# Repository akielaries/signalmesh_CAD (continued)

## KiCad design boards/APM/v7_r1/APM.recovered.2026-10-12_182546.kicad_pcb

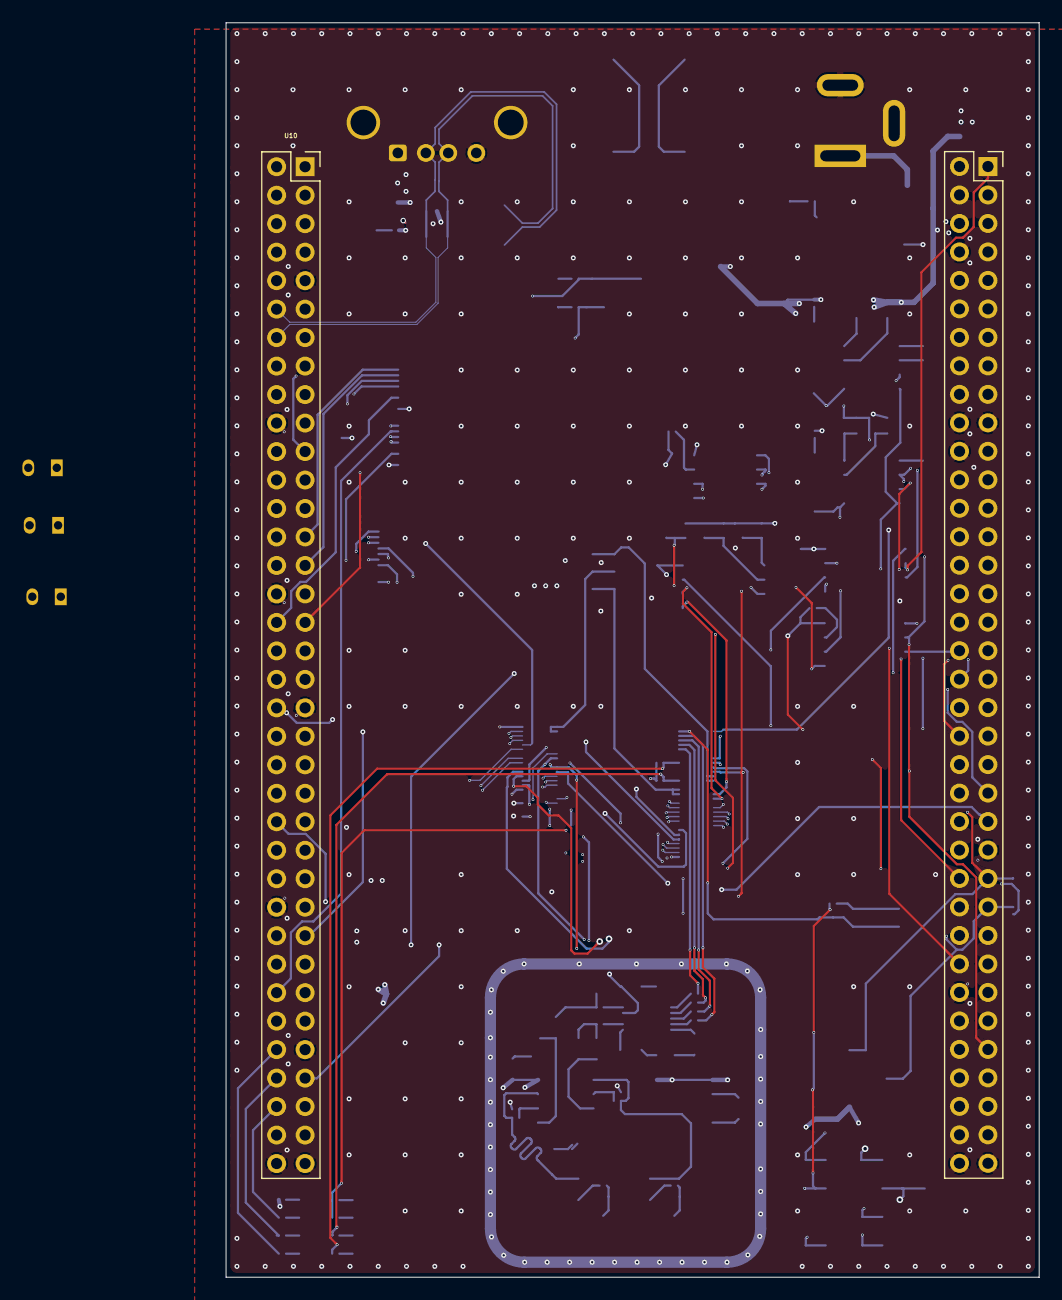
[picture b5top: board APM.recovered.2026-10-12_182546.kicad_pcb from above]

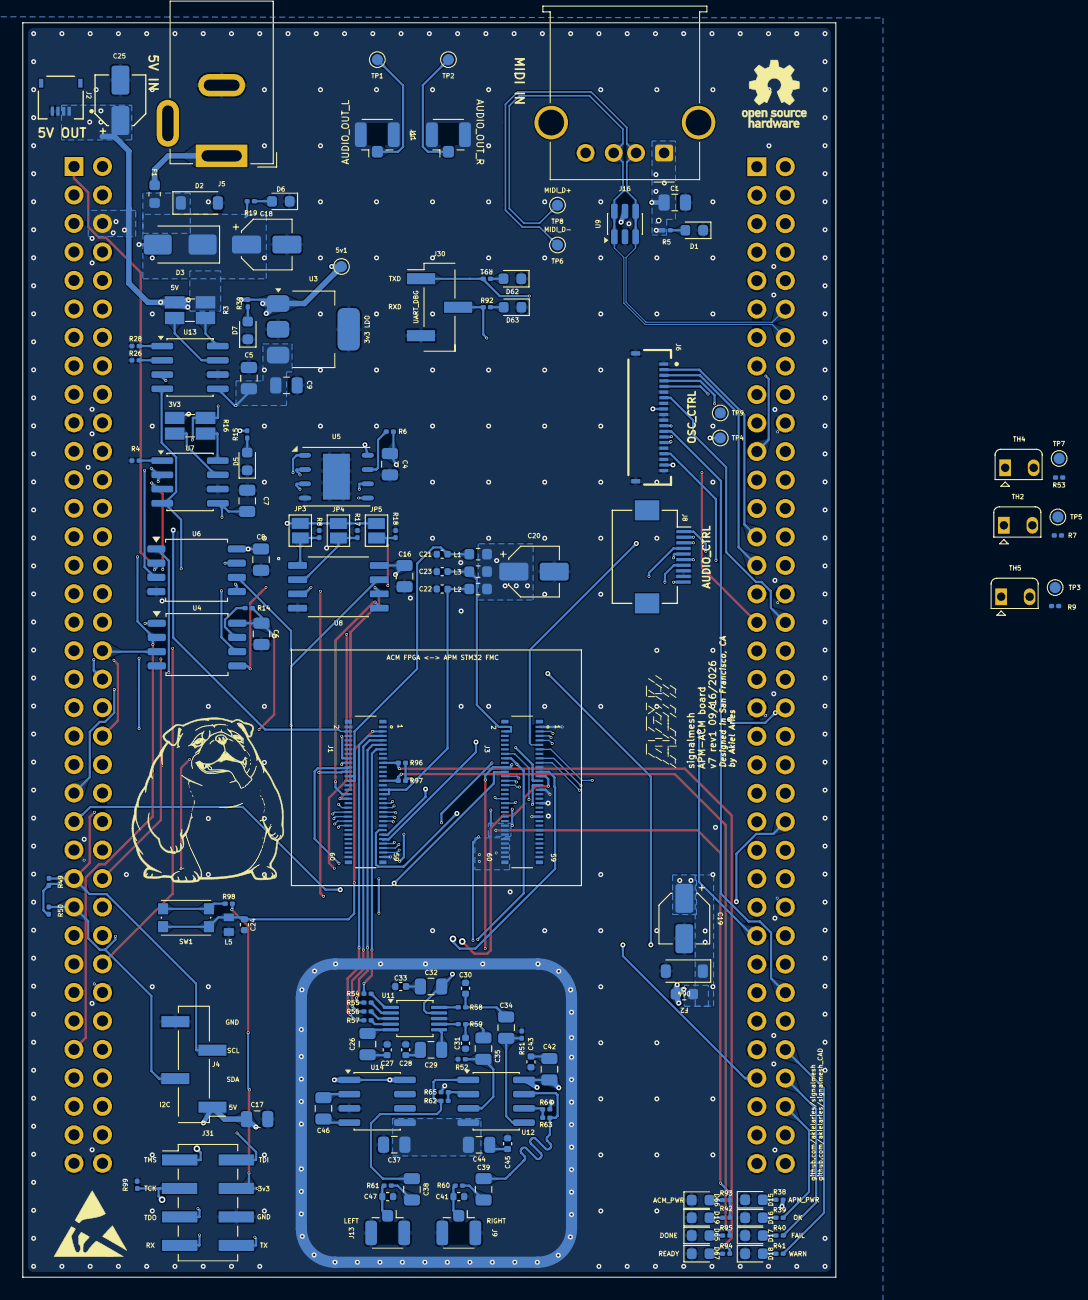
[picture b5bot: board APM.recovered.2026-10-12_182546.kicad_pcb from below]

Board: 6 copper layers, 72.5 x 111.9 mm, 151 parts (149 on the bottom side), 161 nets.

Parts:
5v1: 5v; TestPoint_Pad_D1.0mm
C1: 22pf; C_0805_2012Metric
C4, C6, C8, C9, C16, C17: 100nF; C_0805_2012Metric
C5, C7: 0.1uf; C_0805_2012Metric
C18, C19, C20, C25: 220uF 10V; CP_Elec_4x3
C21, C22, C23, C24: 100nF; C_0402_1005Metric
C26, C29, C32, C34, C35, C38, C39, C42, C44, C46: 10uF; C_0805_2012Metric
C27, C28, C33, C43, C45: 0.1uF; C_0402_1005Metric
C30, C31: 2.7nF; C_0402_1005Metric
C37: 100uF; C_0805_2012Metric
C41, C47: 47pF; C_0402_1005Metric
D1, D5, D7: LED_PWR; LED_0603_1608Metric
D2, D64: 20V 3A; D_SOD-123
D3: SMAJ5.0A; D_SMA
D6: RED_LED_PWR; LED_0603_1608Metric
D15: PWR; LED_0603_1608Metric
D16: OK; LED_0603_1608Metric
D17: FAIL; LED_0603_1608Metric
D18: WARN; LED_0603_1608Metric
D19: FPGA_PWR; LED_0603_1608Metric
D62: TXD; LED_0603_1608Metric
D63: RXD; LED_0603_1608Metric
D65, D66, D67: GREEN_LED; LED_0603_1608Metric
F1, F2: 6V 2A; Fuse_0603_1608Metric
J1, J3: DF40C-60DS-0.4V(51); Hirose_DF40C-60DS-0.4V_2x30_P0.4mm
J2: AUDIO_PWR; AMPHENOL_F3311A7H121004E200
J4: LCD_display; PinHeader_1x04_P2.54mm_Vertical_SMD_Pin1Left
J5: Barrel_Jack; BarrelJack_GCT_DCJ200-10-A_Horizontal
J6: OSC_CTRL; GCT_FFC2B28-20-G
J7: DAC_R_PRB; U.FL_Hirose_U.FL-R-SMT-1_Vertical
J8: AUDIO_CTRL; Hirose_FH12-10S-0.5SH_1x10-1MP_P0.50mm_Horizontal
J9: ACM_DAC_R; U.FL_Hirose_U.FL-R-SMT-1_Vertical
J11: DAC_L_PRB; U.FL_Hirose_U.FL-R-SMT-1_Vertical
J13: ACM_DAC_L; U.FL_Hirose_U.FL-R-SMT-1_Vertical
J16: USB_A_FEMALE; USB_A_Molex_67643_Horizontal
J30: UART_DEBUG; PinHeader_1x03_P2.54mm_Vertical_SMD_Pin1Left
J31: Conn_02x04_Odd_Even; PinHeader_2x04_P2.54mm_Vertical_SMD
JP3: A0; SolderJumper-2_P1.3mm_Open_Pad1.0x1.5mm
JP4: A1; SolderJumper-2_P1.3mm_Open_Pad1.0x1.5mm
JP5: A2; SolderJumper-2_P1.3mm_Open_Pad1.0x1.5mm
L1, L2, L3: PZ1608D300-3R0TF; L_0603_1608Metric
L5: LXES15AAA1-153; INDC1005X45
R3, R16: 0.1; R_Shunt_Ohmite_LVK12
R4, R6, R7, R8, R9, R14, R17, R18, R26, R28, R53: 10k; R_0201_0603Metric
R5, R15, R30, R39, R40, R41, R42, R91, R92: 300; R_0201_0603Metric
R19, R93, R94, R95: 4.7k; R_0201_0603Metric
R38: 1.2k; R_0201_0603Metric
R49, R50: 2.2k; R_0201_0603Metric
R51, R52: 47k; R_0201_0603Metric
R54, R55, R56, R57: 22; R_0201_0603Metric
R58, R59: 560; R_0201_0603Metric
R60, R61: 100; R_0201_0603Metric
R62, R63: 1k; R_0201_0603Metric
R64, R65: 2k; R_0201_0603Metric
R96, R97: 49.9k; R_0201_0603Metric
R98: 100R; R_0201_0603Metric
R99: 5.1K; R_0201_0603Metric
SW1: RST; SW_Push_1P1T_NO_CK_KMR2
TH2, TH4, TH5: 10k; Heraeus_TO-92-2
TP1: DAC_L; TestPoint_Pad_D1.0mm
TP2: DAC_R; TestPoint_Pad_D1.0mm
TP3: THRM_A; TestPoint_Pad_D1.0mm
TP4: FPC_3V3_TP; TestPoint_Pad_D1.0mm
TP5: THRM_C; TestPoint_Pad_D1.0mm
TP6: MIDI_D-; TestPoint_Pad_D1.0mm
TP7: THRM_E; TestPoint_Pad_D1.0mm
TP8: MIDI_D+; TestPoint_Pad_D1.0mm
TP9: FPC_GND_TP; TestPoint_Pad_D1.0mm
U1, U10: PinSocket_2x36_P2.54mm_Vertical
U3: LT1963AxST-3.3; SOT-223-3_TabPin2
U4, U6: W25Q128JVS; SOIC-8_5.3x5.3mm_P1.27mm
U5: MR25H40; DFN-S-8-1EP_6x5mm_P1.27mm
U7, U13: INA219AxD; SOIC-8_3.9x4.9mm_P1.27mm
U8: 24LC1025-I_P; SOIC127P794X202-8N
U9: USBLC6-2SC6; SOT-23-6
U11: CS4344; TSSOP-10_3x3mm_P0.5mm
U12: OPA1656ID; SOIC-8_3.9x4.9mm_P1.27mm
U14: LTC660; SOIC-8_3.9x4.9mm_P1.27mm

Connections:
3V3_APM: C4.1, C6.1, C8.1, C16.1, C32.2, J6.9, J6.19, JP3.2 (B), JP4.2 (B), JP5.2 (B), R6.1, R14.1, R15.2, R16.4, R49.2, R50.2, TP4.1 (1_1), U4.8 (VCC), U5.8 (VDD), U6.8 (VCC), U8.8 (VCC), U11.9 (VA)
3V3_LDO: C5.2, C7.2, C9.1, R16.1, U3.3 (OUT), U7.2 (A0), U7.5 (VS), U13.5 (VS)
5V_APM: 5v1.1 (1_1), C1.2, C17.2, C25.1, C42.2, F2.2, J2.1, J2.2, J4.1, J16.1 (VBUS), R3.4, R5.2, R30.2, R38.2, U1.6 (5V_EXT), U3.1 (IN), U9.5 (VBUS), U12.8 (V+), U14.1 (BOOST), U14.8 (V+)
-5V: C37.1, C44.2, U12.4 (V-), U14.5 (VOUT)
/ADC_POT_1: J6.7, U10.34 (PC4)
/ADC_POT_2: J6.17, U10.36 (PF5)
/APM_DBG_RX: J30.2, R92.1, U10.33 (PA10)
/APM_DBG_TX: J30.1, R91.1, U10.21 (PA9)
/APM_EEPROM_EN: U1.44 (PG3), U8.7 (WP)
/APM_FMC_A16: J3.28, U10.45 (PD11)
/APM_FMC_A17: J3.26, U10.43 (PD12)
/APM_FMC_A18: J3.24, U10.41 (PD13)
/APM_FMC_A19: J3.22, U1.47 (PE3)
/APM_FMC_A20: J1.38, U1.48 (PE4)
/APM_FMC_A21: J1.40, U1.50 (PE5)
/APM_FMC_A22: J1.44, U1.62 (PE6)
/APM_FMC_A23: J1.42, U1.46 (PE2)
/APM_FMC_A24: J1.46, U1.68 (PG13)
/APM_FMC_CLK: J3.34, U1.40 (PD3)
/APM_FMC_DA0: J3.36, U10.46 (PD14)
/APM_FMC_DA1: J1.47, U10.48 (PD15)
/APM_FMC_DA2: J1.41, U1.57 (PD0)
/APM_FMC_DA3: J1.39, U1.55 (PD1)
/APM_FMC_DA4: J3.7, U10.44 (PE7)
/APM_FMC_DA5: J3.5, U10.40 (PE8)
/APM_FMC_DA6: J1.49, U10.52 (PE9)
/APM_FMC_DA7: J3.11, U10.47 (PE10)
/APM_FMC_DA8: J1.51, U10.56 (PE11)
/APM_FMC_DA9: J3.14, U10.49 (PE12)
/APM_FMC_DA10: J3.3, U10.55 (PE13)
/APM_FMC_DA11: J3.15, U10.51 (PE14)
/APM_FMC_DA12: J3.17, U10.53 (PE15)
/APM_FMC_DA13: J1.55, U10.10 (PD8)
/APM_FMC_DA14: J1.43, U1.69 (PD9)
/APM_FMC_DA15: J1.53, U10.65 (PD10)
/APM_FMC_NE1: J3.9, U10.19 (PC7)
/APM_FMC_NL: J1.4, U1.21 (PB7)
/APM_FMC_NOE: J1.35, U1.39 (PD4)
/APM_FMC_NWAIT: J1.57, U10.4 (PC6)
/APM_FMC_NWE: J1.37, U1.41 (PD5)
/APM_FPGA_UART_RX: J3.16, J31.7, U10.23 (PA8)
/APM_FPGA_UART_TX: J3.20, J31.8, U10.31 (PB3)
/APM_I2C2_SCL: J1.34, J4.3, R49.1, U1.51 (PF1), U7.4 (SCL), U8.6 (SCL), U13.4 (SCL)
/APM_I2C2_SDA: J1.32, J4.2, R50.1, U1.53 (PF0), U7.3 (SDA), U8.5 (SDA), U13.3 (SDA)
/APM_LED_FAIL: R40.2, U10.66 (PG8)
/APM_LED_OK: R39.2, U10.68 (PG5)
/APM_LED_WARN: R41.2, U10.64 (PE0)
/APM_MRAM_EN: U1.38 (PC0), U5.3 (~WP)
/APM_SPI1_CS: J1.20, U1.66 (PG10)
/APM_SPI1_MISO: J1.18, U1.63 (PG9), U4.2 (DO/IO_{1}), U5.2 (SO)
/APM_SPI1_MOSI: J1.16, U1.45 (PD7), U4.5 (DI/IO_{0}), U5.5 (SI)
/APM_SPI1_SCK: J1.22, U1.70 (PG11), U4.6 (CLK), U5.6 (SCK)
/APM_SPI2_MISO: J8.3, U10.28 (PB14)
/APM_SPI2_MOSI: J8.2, U10.26 (PB15)
/APM_SPI2_SCK: J8.1, U10.30 (PB13)
/APM_SPIFLASH_EN: U1.36 (PC1), U4.3 (~WP/IO_{2})
/AUD_CS_DAC: J8.4, U1.43 (PD6)
/AUD_CS_POTS: J8.5, U1.52 (PF2)
/AUD_GATE: J8.7, U1.59 (PG0)
/AUD_MODE: J8.6, U1.42 (PG2)
/AUD_SPARE: J8.10, U1.58 (PG1)
/DAC_1-1_R: J7.1 (In), TP2.1 (1_1)
/DAC_1-2_L: J11.1 (In), TP1.1 (1_1)
/FPGA_INTERFACE/A2_JTAG_TDO: J3.25, J31.5
/FPGA_INTERFACE/A3_JTAG_TDI: J3.27, J31.2
/FPGA_INTERFACE/B1_JTAG_TMS: J3.23, J31.1
/FPGA_INTERFACE/C1_JTAG_TCK: J3.21, J31.3, R99.1
/FPGA_INTERFACE/D7_DONE: J1.25, R95.2, R97.1
/FPGA_INTERFACE/E8_READY: J1.17, R94.2, R96.1
/FPGA_INTERFACE/FPGA_3V3: C20.1, J3.46, J3.48, J3.50, J31.4, L1.2, L2.2, L3.2, R42.2, R93.2, R96.2, R97.2, R98.2
/FPGA_INTERFACE/H11_IOT3A_S1: C24.2, J1.3, L5.2, SW1.2
/FPGA_INTERFACE/LED_DONE_A: D65.2 (A), R95.1
/FPGA_INTERFACE/LED_PWR_A: D66.2 (A), R93.1
/FPGA_INTERFACE/LED_READY_A: D67.2 (A), R94.1
/FPGA_INTERFACE/RST_NODE: R98.1, SW1.1
/FPGA_INTERFACE/VCCIO01: C21.1, J1.24, J1.26, L1.1
/FPGA_INTERFACE/VCCIO23: C23.2, J3.2, J3.4, L3.1
/FPGA_INTERFACE/VCCIO67: C22.2, J1.29, J1.31, L2.1
/MIDI_FS_D+: J16.3 (D+), TP8.1 (1_1), U9.1 (I/O1), U9.6 (I/O1), U10.14 (PA11)
/MIDI_FS_D-: J16.2 (D-), TP6.1 (1_1), U9.3 (I/O2), U9.4 (I/O2), U10.12 (PA12)
/NC: U1.25 (PC14), U1.27 (PC15), U1.29 (PH0)
/PMS_APM/5V_PWR_IN: C18.1, D2.1 (K), D3.1 (K), F1.1, R3.1, R19.2
/QSPI1_D0: U6.5 (DI/IO_{0}), U10.1 (PC9)
/QSPI1_D1: U1.1 (PC10), U6.2 (DO/IO_{1})
/QSPI1_D2: U1.11 (PF7), U6.3 (~WP/IO_{2})
/QSPI1_D3: U1.30 (PA1), U6.7 (~HOLD/~RESET/IO_{3})
/QSPI1_NCS: U6.1 (~CS), U10.70 (PG6)
/QSPI_SCK2: U6.6 (CLK), U10.42 (PF10)
/SEL_A_BIT_0: J6.2, U10.27 (PB4)
/SEL_A_BIT_1: J6.3, U10.29 (PB5)
/SEL_A_BIT_2: J6.4, U10.24 (PB1)
/SEL_A_BIT_3: J6.5, U10.17 (PB6)
/SEL_B_BIT_0: J6.12, U10.16 (PB12)
/SEL_B_BIT_1: J6.13, U10.60 (PF15)
/SEL_B_BIT_2: J6.14, U10.13 (PA6)
/SEL_B_BIT_3: J6.15, U10.15 (PA7)
/SPIFLASH_CS: U1.34 (PB0), U4.1 (~CS)
/SPIMRAM_CS: U1.28 (PA0), U5.1 (~CS)
/THRM_A: R9.2, TP3.1 (1_1)
/THRM_C: R7.2, TP5.1 (1_1)
/THRM_E: R53.2, TP7.1 (1_1)
ACM_DAC_LRCK: J1.7, R56.1
ACM_DAC_MCLK: J1.5, R57.1
ACM_DAC_SCLK: J1.9, R55.1
ACM_DAC_SDIN: J1.11, R54.1
FPGA_5V: C19.1, D64.1 (K), F2.1, J3.52, J3.54, J3.56, J3.58, J3.60
GND: C1.1, C4.2, C5.1, C6.2, C7.1, C8.2, C9.2, C16.2, C17.1, C18.2, C19.2, C20.2, C21.2, C22.1, C23.1, C24.1, C25.2, C27.1, C28.1, C30.1, C31.1, C33.1, C37.2, C41.1, C43.1, C45.1, C47.1, D1.1 (K), D2.2 (A), D3.2 (A), D5.1 (K), D6.1 (K), D7.1 (K), D15.1 (K), D16.1 (K), D17.1 (K), D18.1 (K), D19.1 (K), D62.1 (K), D63.1 (K), D64.2 (A), D65.1 (K), D66.1 (K), D67.1 (K), J1.1, J1.2, J1.15, J1.27, J1.28, J1.45, J1.50, J1.59, J1.60, J2.3, J2.4, J3.1, J3.19, J3.29, J3.35, J3.41, J3.47, J3.53, J3.59, J4.4, J5.2, J6.1, J6.6, J6.8, J6.10, J6.11, J6.16, J6.18, J6.20, J6.S1 (SHIELD), J6.S2 (SHIELD), J7.2 (Ext), J8.8, J8.9, J9.2 (Ext), J11.2 (Ext), J13.2 (Ext), J16.4 (GND), J30.3, J31.6, L5.1, R4.1, R8.2, R17.2, R18.2, R26.1, R28.1, R51.2, R52.2, R64.2, R65.2, R99.2, TH2.1, TH4.1, TH5.1, TP9.1 (1_1), U1.8 (GND_CN11), U1.19 (GND_CN11), U1.20 (GND_CN11), U1.22 (GND_CN11), U1.49 (GND_CN11), U1.60 (GND_CN11), U1.71 (GND_CN11), U1.72 (GND_CN11), U3.2 (GND), U4.4 (GND), U5.4 (VSS), U5.9 (PAD), U6.4 (GND), U7.6 (GND), U8.4 (VSS), U9.2 (GND), U10.9 (GND_CN12), U10.20 (GND_CN12), U10.32 (AGND_CN12), U10.39 (GND_CN12), U10.54 (GND_CN12), U10.63 (GND_CN12), U10.71 (GND_CN12), U10.72 (GND_CN12), U11.8 (GND), U13.6 (GND), U14.3 (GND)
unnamed: C26.1, C27.2
unnamed: C28.2, C29.1
unnamed: C30.2, C34.2, R58.2
unnamed: C31.2, C35.2, R59.2
unnamed: C32.1, C33.2
unnamed: C38.1, R61.1
unnamed: C38.2, R62.1, U12.1
unnamed: C39.1, R60.1
unnamed: C39.2, R63.1, U12.7
unnamed: C42.1, C43.2
unnamed: C44.1, C45.2
unnamed: D1.2 (A), R5.1
unnamed: D5.2 (A), R15.1
unnamed: D6.2 (A), R19.1
unnamed: D7.2 (A), R30.1
unnamed: D15.2 (A), R38.1
unnamed: D16.2 (A), R39.1
unnamed: D17.2 (A), R40.1
unnamed: D18.2 (A), R41.1
unnamed: D19.2 (A), R42.1
unnamed: D62.2 (A), R91.2
unnamed: D63.2 (A), R92.2
unnamed: F1.2, J5.1
unnamed: C41.2, J9.1 (In), R60.2
unnamed: C47.2, J13.1 (In), R61.2
unnamed: JP3.1 (A), R8.1, U8.1 (A0)
unnamed: JP4.1 (A), R17.1, U8.2 (A1)
unnamed: JP5.1 (A), R18.1, U8.3 (A2)
unnamed: R7.1, TH2.2
unnamed: R9.1, TH5.2
unnamed: R53.1, TH4.2
unnamed: R14.2, U4.7 (~HOLD/~RESET/IO_{3})
unnamed: R6.2, U5.7 (~HOLD)
unnamed: R4.2, U7.1 (A1)
unnamed: R16.2, U7.8 (IN+)
unnamed: R16.3, U7.7 (IN-)
unnamed: R59.1, U11.7 (AOUTL)
unnamed: R58.1, U11.10 (AOUTR)
unnamed: C29.2, U11.6 (FILT+)
unnamed: R56.2, U11.3 (LRCK)
unnamed: R57.2, U11.4 (MCLK)
unnamed: R54.2, U11.1 (SDIN)
unnamed: C26.2, U11.5 (VQ)
unnamed: R55.2, U11.2 (~DEM/SCLK)
unnamed: C35.1, R52.1, U12.3 (+)
unnamed: R62.2, R65.1, U12.2 (-)
unnamed: C34.1, R51.1, U12.5 (+)
unnamed: R63.2, R64.1, U12.6 (-)
unnamed: R26.2, U13.2 (A0)
unnamed: R28.2, U13.1 (A1)
unnamed: R3.2, U13.8 (IN+)
unnamed: R3.3, U13.7 (IN-)
unnamed: C46.1, U14.2 (CAP+)
unnamed: C46.2, U14.4 (CAP-)

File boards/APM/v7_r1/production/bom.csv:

Designator,Footprint,Quantity,Value,LCSC Part #
5V1,TestPoint_Pad_D1.0mm,1,5v,
C1,0805,1,22pf,
"C16, C17, C4, C6, C8, C9",0805,6,100nF,
"C18, C19, C20, C25",CP_Elec_4x3,4,220uF 10V,
"C21, C22, C23, C24",0402,4,100nF,
"C26, C29, C32, C34, C35, C38, C39, C42, C44, C46",0805,10,10uF,
"C27, C28, C33, C43, C45",0402,5,0.1uF,
"C30, C31",0402,2,2.7nF,
C37,0805,1,100uF,
"C41, C47",0402,2,47pF,
"C5, C7",0805,2,0.1uf,
"D1, D5, D7",0603,3,LED_PWR,
D15,0603,1,PWR,
D16,0603,1,OK,
D17,0603,1,FAIL,
D18,0603,1,WARN,
D19,0603,1,FPGA_PWR,
"D2, D64",D_SOD-123,2,20V 3A,
D3,D_SMA,1,SMAJ5.0A,
D6,0603,1,RED_LED_PWR,
D62,0603,1,TXD,
D63,0603,1,RXD,
"D65, D66, D67",0603,3,GREEN_LED,
"F1, F2",0603,2,6V 2A,
"J1, J3",Hirose_DF40C-60DS-0.4V_2x30_P0.4mm,2,DF40C-60DS-0.4V(51),
J11,U.FL_Hirose_U.FL-R-SMT-1_Vertical,1,DAC_L_PRB,
J13,U.FL_Hirose_U.FL-R-SMT-1_Vertical,1,ACM_DAC_L,
J16,USB_A_Molex_67643_Horizontal,1,USB_A_FEMALE,
J2,AMPHENOL_F3311A7H121004E200,1,AUDIO_PWR,
J30,PinHeader_1x03_P2.54mm_Vertical_SMD_Pin1Left,1,UART_DEBUG,
J31,PinHeader_2x04_P2.54mm_Vertical_SMD,1,Conn_02x04_Odd_Even,
J4,PinHeader_1x04_P2.54mm_Vertical_SMD_Pin1Left,1,LCD_display,
J5,BarrelJack_GCT_DCJ200-10-A_Horizontal,1,Barrel_Jack,
J6,GCT_FFC2B28-20-G,1,OSC_CTRL,
J7,U.FL_Hirose_U.FL-R-SMT-1_Vertical,1,DAC_R_PRB,
J8,Hirose_FH12-10S-0.5SH_1x10-1MP_P0.50mm_Horizontal,1,AUDIO_CTRL,
J9,U.FL_Hirose_U.FL-R-SMT-1_Vertical,1,ACM_DAC_R,
JP3,SolderJumper-2_P1.3mm_Open_Pad1.0x1.5mm,1,A0,
JP4,SolderJumper-2_P1.3mm_Open_Pad1.0x1.5mm,1,A1,
JP5,SolderJumper-2_P1.3mm_Open_Pad1.0x1.5mm,1,A2,
"L1, L2, L3",0603,3,PZ1608D300-3R0TF,
L5,INDC1005X45,1,LXES15AAA1-153,
"R14, R17, R18, R26, R28, R4, R6, R8",0201,8,10k,
"R15, R30, R39, R40, R41, R42, R5, R91, R92",0201,9,300,
"R16, R3",R_Shunt_Ohmite_LVK12,2,0.1,
"R19, R93, R94, R95",0201,4,4.7k,
R38,0201,1,1.2k,
"R49, R50",0201,2,2.2k,
"R51, R52",0201,2,47k,
"R54, R55, R56, R57",0201,4,22,
"R58, R59",0201,2,560,
"R60, R61",0201,2,100,
"R62, R63",0201,2,1k,
"R64, R65",0201,2,2k,
"R96, R97",0201,2,49.9k,
R98,0201,1,100R,
R99,0201,1,5.1K,
SW1,SW_Push_1P1T_NO_CK_KMR2,1,RST,
TP1,TestPoint_Pad_D1.0mm,1,DAC_L,
TP2,TestPoint_Pad_D1.0mm,1,DAC_R,
TP4,TestPoint_Pad_D1.0mm,1,FPC_3V3_TP,
TP6,TestPoint_Pad_D1.0mm,1,MIDI_D-,
TP8,TestPoint_Pad_D1.0mm,1,MIDI_D+,
TP9,TestPoint_Pad_D1.0mm,1,FPC_GND_TP,
"U1, U10",PinSocket_2x36_P2.54mm_Vertical,2,~,
U11,TSSOP-10_3x3mm_P0.5mm,1,CS4344,
U12,SOIC-8_3.9x4.9mm_P1.27mm,1,OPA1656ID,
"U13, U7",SOIC-8_3.9x4.9mm_P1.27mm,2,INA219AxD,
U14,SOIC-8_3.9x4.9mm_P1.27mm,1,LTC660,
U3,SOT-223-3_TabPin2,1,LT1963AxST-3.3,
"U4, U6",SOIC-8_5.3x5.3mm_P1.27mm,2,W25Q128JVS,
U5,DFN-S-8-1EP_6x5mm_P1.27mm,1,MR25H40,
U8,SOIC127P794X202-8N,1,24LC1025-I_P,
U9,SOT-23-6,1,USBLC6-2SC6,

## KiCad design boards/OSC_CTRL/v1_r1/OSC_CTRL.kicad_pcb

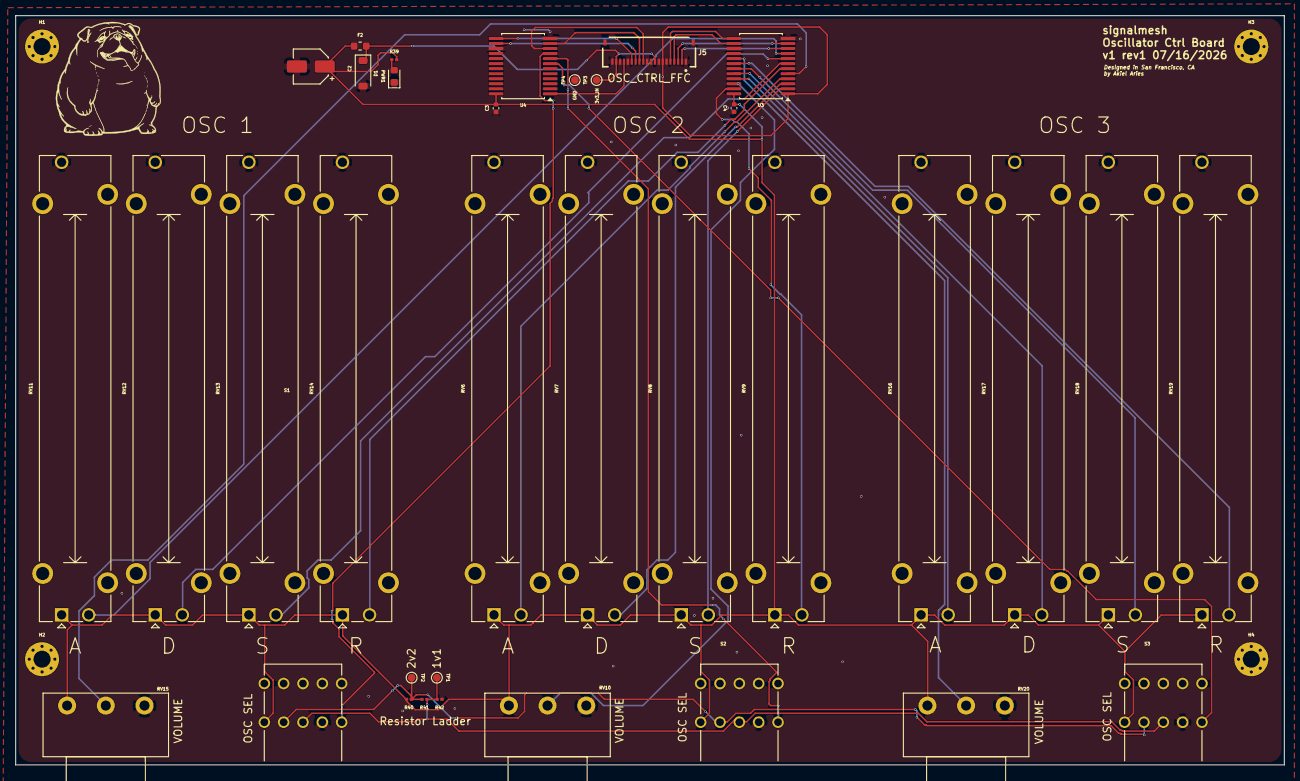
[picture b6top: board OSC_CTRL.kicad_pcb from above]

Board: 2 copper layers, 164.0 x 96.8 mm, 39 parts (0 on the bottom side), 34 nets.

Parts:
C2: 220uF 10V; CP_Elec_4x3
C3, C4: 100nF; C_0402_1005Metric
D1: 20V 3A; D_SOD-123
F2: 4V 2A; Fuse_0603_1608Metric
H1, H2, H3, H4: M2; MountingHole_2.2mm_M2_Pad_Via
J5: OSC_CTRL; GCT_FFC2B28-20-G
PWR1: GREEN_LED; LED_0603_1608Metric
R39: 4.7k; R_0201_0603Metric
R40, R41, R42: 10K; R_0201_0603Metric
RV6, RV7, RV8, RV9, RV11, RV12, RV13, RV14, RV16, RV17, RV18, RV19: 10K; Potentiometer_Bourns_PTA4543_Single_Slide
RV10, RV15, RV20: 10K; Potentiometer_Piher_PC-16_Single_Horizontal
S1, S2, S3: SRBM149501; SW_SRBM149501
TP1: 1v1; TestPoint_Pad_D1.0mm
TP2: 2v2; TestPoint_Pad_D1.0mm
TP3: FPC_3V3_TP; TestPoint_Pad_D1.0mm
TP4: FPC_GND_TP; TestPoint_Pad_D1.0mm
U3, U4: CD74HC4067SM; SSOP-24_5.3x8.2mm_P0.65mm

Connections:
3V3: C2.1, C3.2, C4.2, F2.1, R39.2, R40.2, RV6.1, RV7.1, RV8.1, RV9.1, RV10.1, RV11.1, RV12.1, RV13.1, RV14.1, RV15.1, RV16.1, RV17.1, RV18.1, RV19.1, RV20.1, S1.5F, S2.5F, S3.5F, U3.24 (VCC), U4.24 (VCC)
3V3_IN: D1.1 (K), F2.2, J5.9, J5.19, TP3.1 (1_1)
/NODE_A: R40.1, R41.2, S1.4F, S2.4F, S3.4F, TP2.1 (1_1)
/NODE_B: R41.1, R42.2, S1.3F, S2.3F, S3.3F, TP1.1 (1_1)
/OSC_1_ATK: RV11.2, U3.9 (I0)
/OSC_1_DEC: RV12.2, U3.8 (I1)
/OSC_1_REL: RV14.2, U3.6 (I3)
/OSC_1_SUS: RV13.2, U3.7 (I2)
/OSC_1_VOL: RV15.2, U3.5 (I4)
/OSC_1_WAVE: S1.1F, U4.9 (I0)
/OSC_2_ATK: RV6.2, U3.4 (I5)
/OSC_2_DEC: RV7.2, U3.3 (I6)
/OSC_2_REL: RV9.2, U3.23 (I8)
/OSC_2_SUS: RV8.2, U3.2 (I7)
/OSC_2_VOL: RV10.2, U3.22 (I9)
/OSC_2_WAVE: S2.1F, U4.8 (I1)
/OSC_3_ATK: RV16.2, U3.21 (I10)
/OSC_3_DEC: RV17.2, U3.20 (I11)
/OSC_3_REL: RV19.2, U3.18 (I13)
/OSC_3_SUS: RV18.2, U3.19 (I12)
/OSC_3_VOL: RV20.2, U3.17 (I14)
/OSC_3_WAVE: S3.1F, U4.7 (I2)
/SEL_A_BIT_0: J5.2, U3.10 (S0)
/SEL_A_BIT_1: J5.3, U3.11 (S1)
/SEL_A_BIT_2: J5.4, U3.14 (S2)
/SEL_A_BIT_3: J5.5, U3.13 (S3)
/SEL_B_BIT_0: J5.12, U4.10 (S0)
/SEL_B_BIT_1: J5.13, U4.11 (S1)
/SEL_B_BIT_2: J5.14, U4.14 (S2)
/SEL_B_BIT_3: J5.15, U4.13 (S3)
/STM32_ADC_1_10: J5.7, U3.1 (COM)
/STM32_ADC_3_1: J5.17, U4.1 (COM)
GND: C2.2, C3.1, C4.1, D1.2 (A), J5.1, J5.6, J5.8, J5.10, J5.11, J5.16, J5.18, J5.20, J5.S1 (SHIELD), J5.S2 (SHIELD), PWR1.1 (K), R42.1, RV6.3, RV7.3, RV8.3, RV9.3, RV10.3, RV11.3, RV12.3, RV13.3, RV14.3, RV15.3, RV16.3, RV17.3, RV18.3, RV19.3, RV20.3, S1.2F, S2.2F, S3.2F, TP4.1 (1_1), U3.12 (GND), U3.15 (~E), U4.12 (GND), U4.15 (~E)
unnamed: PWR1.2 (A), R39.1
